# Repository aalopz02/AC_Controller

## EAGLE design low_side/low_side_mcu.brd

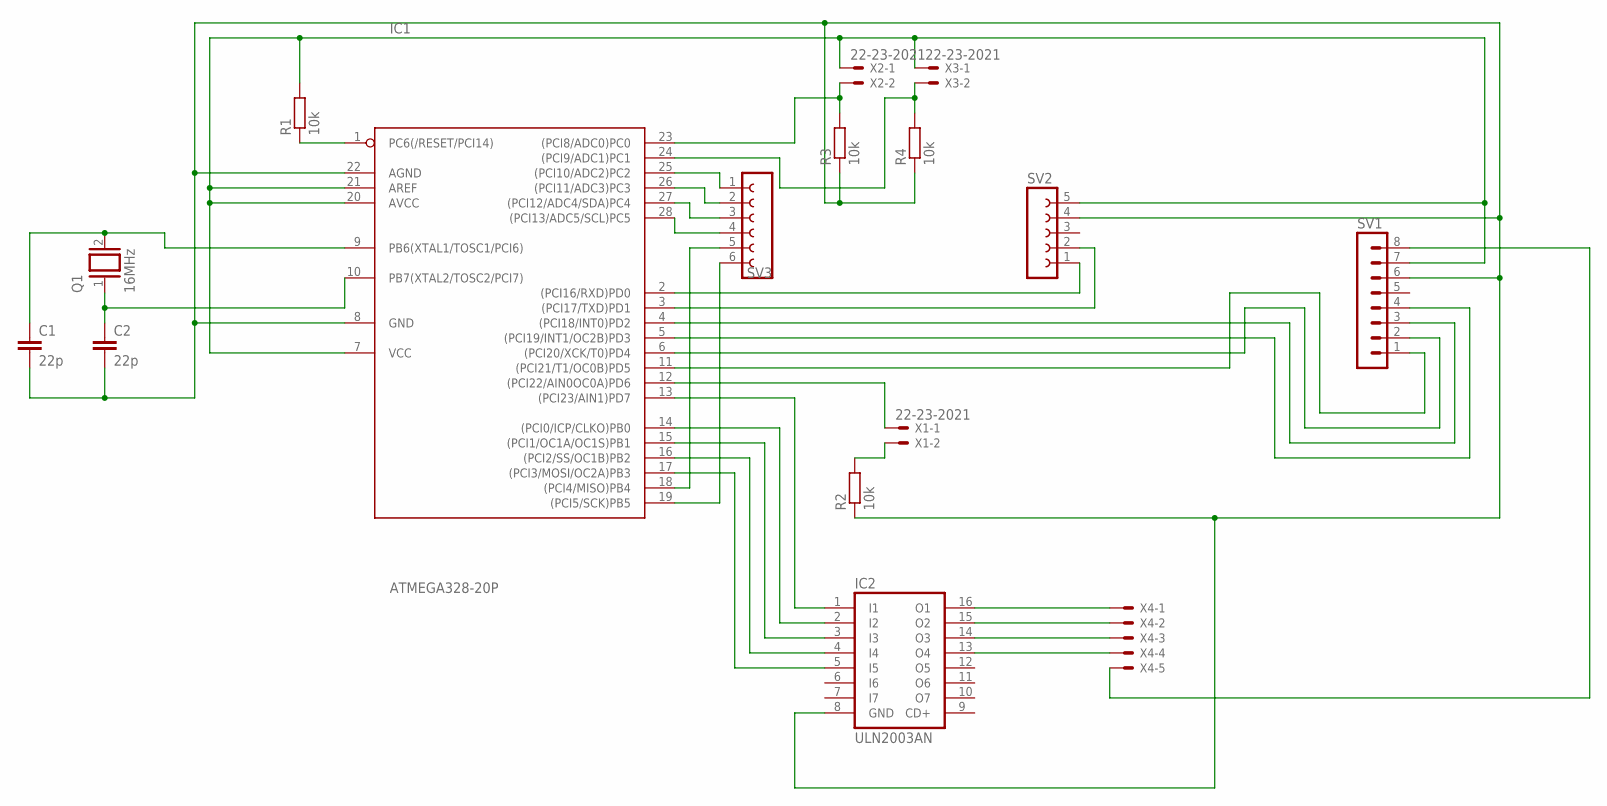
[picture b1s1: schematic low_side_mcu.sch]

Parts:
C1, C2: 22p; C025-024X044
IC1: ATMEGA328-20P; DIL28-3
IC2: ULN2003AN; DIL16
Q1: 16MHz; Q
R1, R2, R3, R4: 10k; 0204/5
SV1: MA08-1
SV2: FE05-1
SV3: FE06-1; FE06
X1, X2, X3: 22-23-2021
X4: KK-156-5

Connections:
unnamed: IC1.7 (VCC), IC1.20 (AVCC), IC1.21 (AREF), R1.2, SV1.7, SV2.5, X2.1, X3.1
unnamed: IC1.1 (PC6(/RESET/PCI14)), R1.1
unnamed: C1.1, IC1.9 (PB6(XTAL1/TOSC1/PCI6)), Q1.2
unnamed: C2.1, IC1.10 (PB7(XTAL2/TOSC2/PCI7)), Q1.1
unnamed: IC1.11 ((PCI21/T1/OC0B)PD5), SV1.1
unnamed: IC1.12 ((PCI22/AIN0OC0A)PD6), X1.1
unnamed: IC1.4 ((PCI18/INT0)PD2), SV1.3
unnamed: IC1.5 ((PCI19/INT1/OC2B)PD3), SV1.4
unnamed: IC1.6 ((PCI20/XCK/T0)PD4), SV1.2
unnamed: IC1.2 ((PCI16/RXD)PD0), SV2.1
unnamed: IC1.3 ((PCI17/TXD)PD1), SV2.2
unnamed: R2.2, X1.2
unnamed: IC1.23 ((PCI8/ADC0)PC0), R3.2, X2.2
unnamed: IC2.16 (O1), X4.1
unnamed: IC1.13 ((PCI23/AIN1)PD7), IC2.1 (I1)
unnamed: IC1.14 ((PCI0/ICP/CLKO)PB0), IC2.2 (I2)
unnamed: IC1.24 ((PCI9/ADC1)PC1), R4.2, X3.2
unnamed: IC1.15 ((PCI1/OC1A/OC1S)PB1), IC2.3 (I3)
unnamed: IC1.16 ((PCI2/SS/OC1B)PB2), IC2.4 (I4)
unnamed: IC1.17 ((PCI3/MOSI/OC2A)PB3), IC2.5 (I5)
unnamed: IC2.15 (O2), X4.2
unnamed: IC2.14 (O3), X4.3
unnamed: IC2.13 (O4), X4.4
unnamed: SV1.8, X4.5
unnamed: IC1.25 ((PCI10/ADC2)PC2), SV3.1
unnamed: IC1.26 ((PCI11/ADC3)PC3), SV3.2
unnamed: IC1.27 ((PCI12/ADC4/SDA)PC4), SV3.3
unnamed: IC1.28 ((PCI13/ADC5/SCL)PC5), SV3.4
unnamed: IC1.18 ((PCI4/MISO)PB4), SV3.5
unnamed: IC1.19 ((PCI5/SCK)PB5), SV3.6
unnamed: C1.2, C2.2, IC1.8 (GND), IC1.22 (AGND), IC2.8 (GND), R2.1, R3.1, R4.1, SV1.6, SV2.4

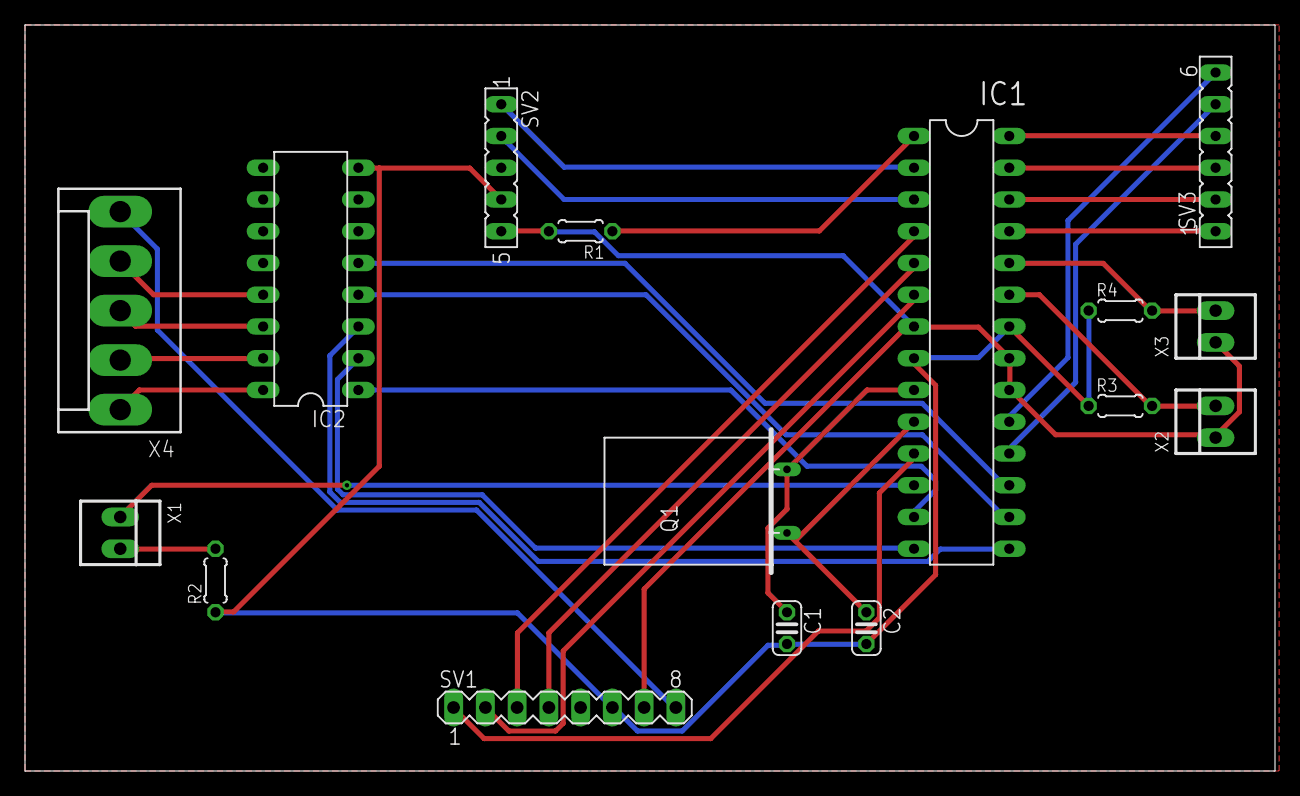
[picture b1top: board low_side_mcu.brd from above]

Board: 2 copper layers, 100.0 x 59.7 mm, 16 parts (0 on the bottom side), 31 nets.

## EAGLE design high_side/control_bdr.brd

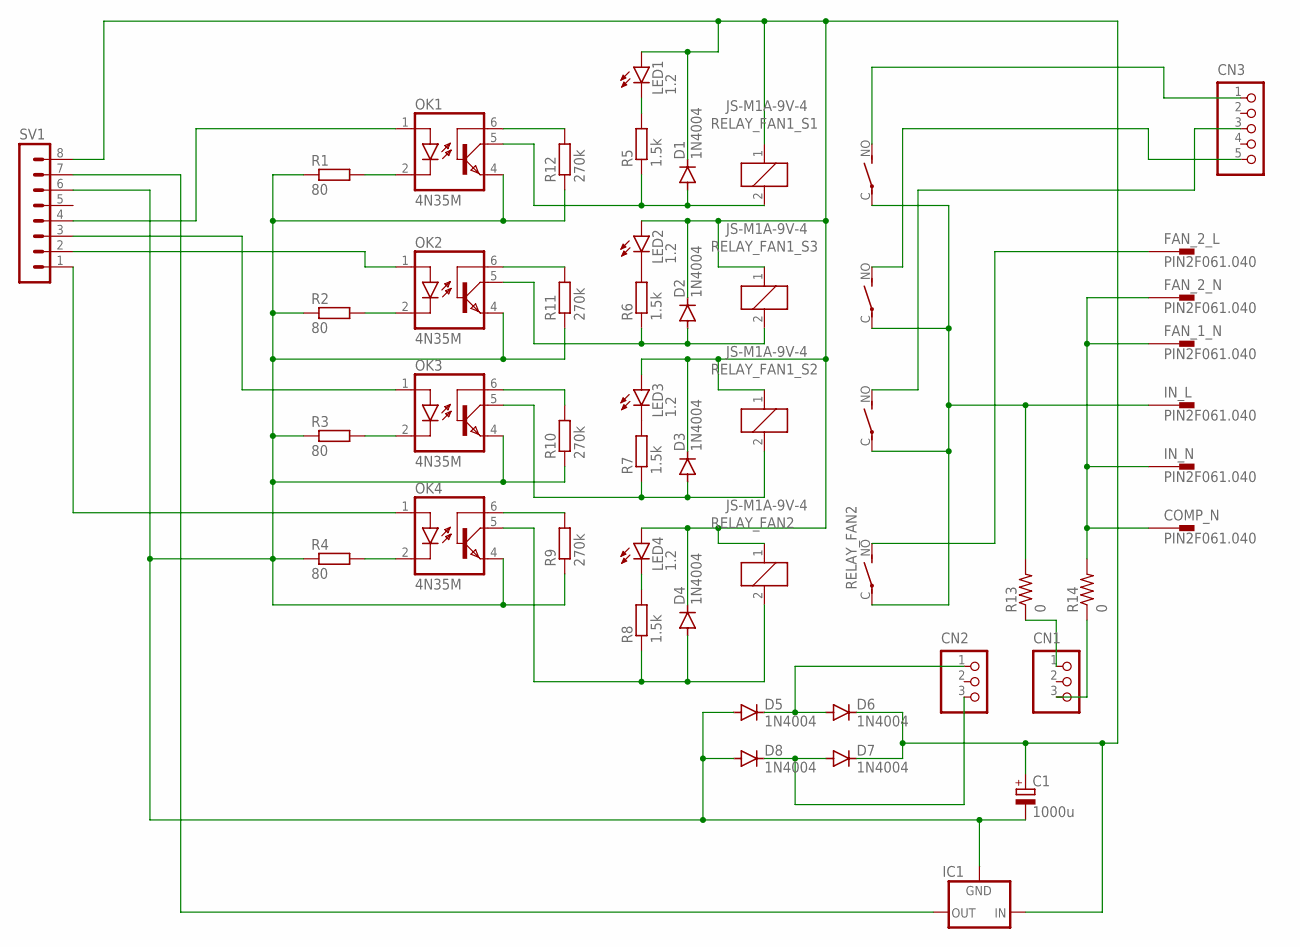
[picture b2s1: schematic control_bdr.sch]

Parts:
C1: 1000u; E3,5-10
CN1: B3P-VH
CN2: B3B-XASK-1
CN3: B5P-VH
COMP_N: PIN2F061.040; F061.040
D1, D2, D3, D4, D5, D6, D7, D8: 1N4004; DO41-10
FAN_1_N, FAN_2_L, FAN_2_N: PIN2F061.040; F061.040
IC1: 78XXL
IN_L: PIN2F061.040; F061.040
IN_N: PIN2F061.040; F061.040
LED1, LED2, LED3, LED4: 1.2; LED5MM
OK1, OK2, OK3, OK4: 4N35M; DIL06
R1, R2, R3, R4: 80; 0204/7
R5, R6, R7, R8: 1.5k; 0204/7
R9, R10, R11, R12: 270k; 0204/7
R13, R14: 0; 0204V
RELAY_FAN1_S1, RELAY_FAN1_S2, RELAY_FAN1_S3, RELAY_FAN2: JS-M1A-9V-4; JS-M1A
SV1: MA08-1

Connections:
unnamed: IN_L.A1, IN_L.A2, R13.2, RELAY_FAN1_S1.C, RELAY_FAN1_S2.C, RELAY_FAN1_S3.C, RELAY_FAN2.C
unnamed: CN3.1, RELAY_FAN1_S1.NO (S)
unnamed: CN3.5, RELAY_FAN1_S3.NO (S)
unnamed: CN3.3, RELAY_FAN1_S2.NO (S)
unnamed: FAN_2_L.A1, FAN_2_L.A2, RELAY_FAN2.NO (S)
unnamed: COMP_N.A1, COMP_N.A2, FAN_1_N.A1, FAN_1_N.A2, FAN_2_N.A1, FAN_2_N.A2, IN_N.A1, IN_N.A2, R14.2
unnamed: OK1.2 (C), R1.2
unnamed: OK2.2 (C), R2.2
unnamed: OK3.2 (C), R3.2
unnamed: OK4.2 (C), R4.2
unnamed: C1.-, D5.A, D8.A, IC1.GND, OK1.4 (EMI), OK2.4 (EMI), OK3.4 (EMI), OK4.4 (EMI), R1.1, R2.1, R3.1, R4.1, R9.1, R10.1, R11.1, R12.1, SV1.6
unnamed: LED2.K (C), R6.2
unnamed: LED1.K (C), R5.2
unnamed: LED3.K (C), R7.2
unnamed: LED4.K (C), R8.2
unnamed: CN1.1, R13.1
unnamed: CN1.3, R14.1
unnamed: OK4.6 (BAS), R9.2
unnamed: OK3.6 (BAS), R10.2
unnamed: OK2.6 (BAS), R11.2
unnamed: OK1.6 (BAS), R12.2
unnamed: CN2.1, D5.C, D6.A
unnamed: IC1.OUT, SV1.7
unnamed: CN2.3, D7.A, D8.C
unnamed: OK2.1 (A), SV1.2
unnamed: D4.A, OK4.5 (COL), R8.1, RELAY_FAN2.2
unnamed: D3.A, OK3.5 (COL), R7.1, RELAY_FAN1_S2.2
unnamed: D2.A, OK2.5 (COL), R6.1, RELAY_FAN1_S3.2
unnamed: D1.A, OK1.5 (COL), R5.1, RELAY_FAN1_S1.2
unnamed: OK1.1 (A), SV1.4
unnamed: OK3.1 (A), SV1.3
unnamed: OK4.1 (A), SV1.1
unnamed: C1.+, D1.C, D2.C, D3.C, D4.C, D6.C, D7.C, IC1.IN, LED1.A, LED2.A, LED3.A, LED4.A, RELAY_FAN1_S1.1, RELAY_FAN1_S2.1, RELAY_FAN1_S3.1, RELAY_FAN2.1, SV1.8

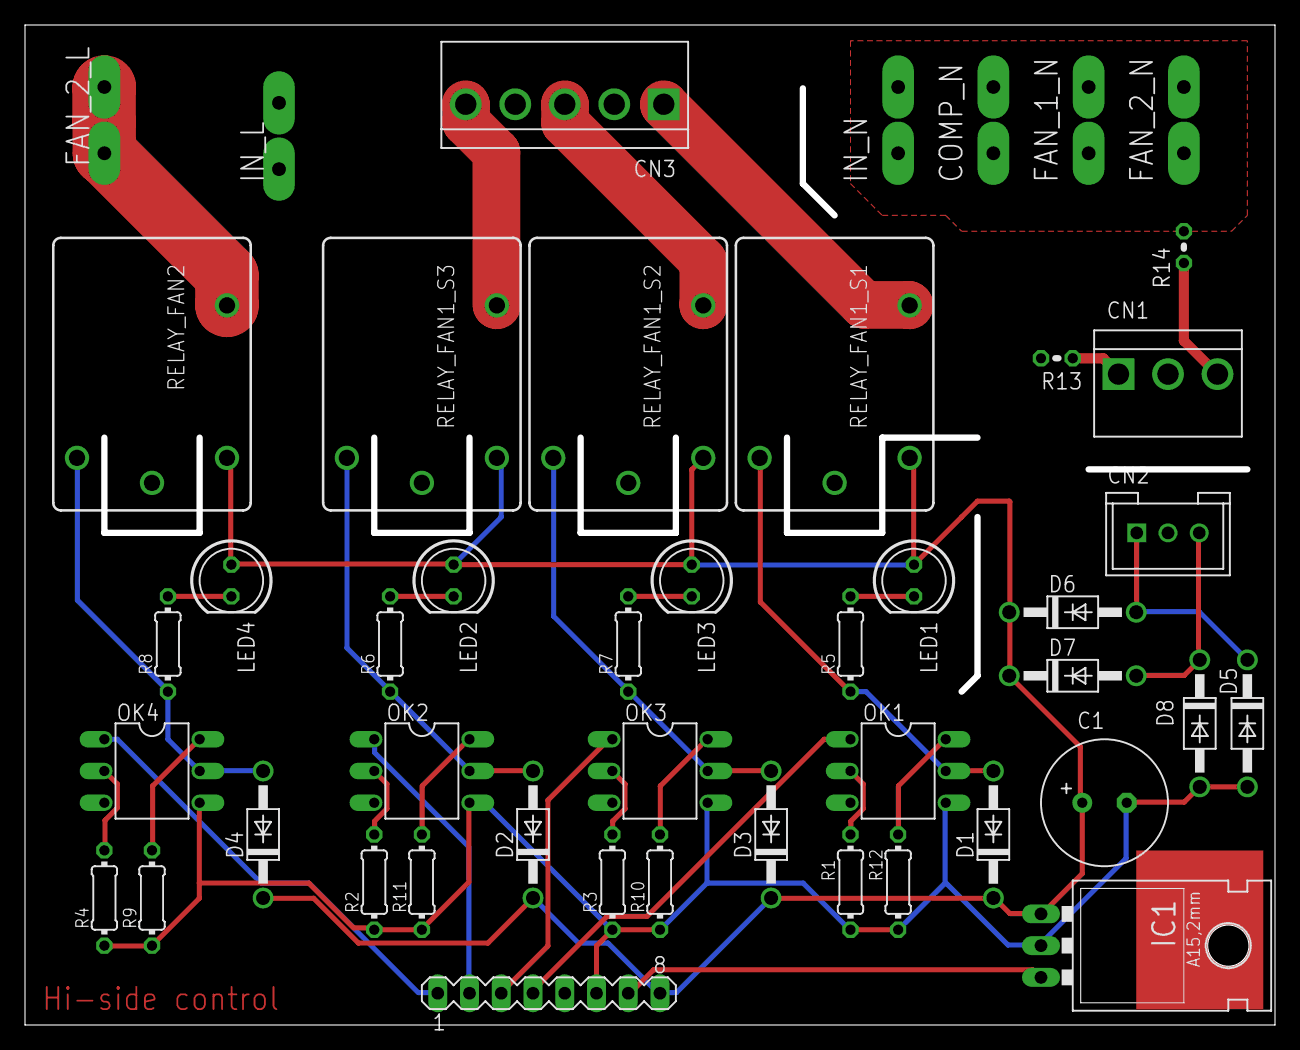
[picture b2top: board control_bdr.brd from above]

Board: 2 copper layers, 99.5 x 79.5 mm, 46 parts (0 on the bottom side), 33 nets.

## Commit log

2024-03-17 Add to git
2024-06-23 Rework dirs
2024-06-23 Start control page
